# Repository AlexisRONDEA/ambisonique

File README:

Projet : Ambisonique
  
Collaborateurs : RONDEAU Alexis, SOULE Zeïck, BODET Amaury, VAN DE MOOSDIJK Martina, MILLASSEAU Adrien, LATHUILLERE Colin

	I / Introduction
	
Ce projet, initialement conçu par des troisièmes années, permet de connecter huit enceintes pour délivrer un son provenant de différentes directions.
Nos objectifs concernent l’encombrement et la qualité sonore de l’amplificateur audio. En effet, les enceintes sont pour l’instant alimentées par des alimentations de laboratoire, ce qui est peu pratique et prend de la place. De plus, le signal audio est transmis par un seul fil. Cette liaison asymétrique est la source de parasite sur le signal et donne lieu à une mauvaise qualité sonore. 
On se propose donc de remplacer la transmission du signal par une liaison symétrique différentielle, pour supprimer le plus de parasites possible. On change l’amplificateur actuel par un amplificateur de classe D pour améliorer la qualité sonore du signal en sortie. Enfin, on fait passer l’alimentation des enceintes par le câble transmettant le signal audio, pour alimenter les enceintes avec le réseau.
Pour cela on sépare ce projet en quatre modules et en deux PCB. Les deux premiers appartiendront au premier et le séparateur avec l’ampli audio seront sur le deuxième PCB.

Objectifs : 
- Créer un module modifiant le courant d'entrée du réseau 230V AC en 24V DC
- Créer un module qui additionne la partie continue de 24V au signal
- Créer un module qui sépare le signal et la puissance pour alimenter les enceintes
- Créer l’amplificateur de classe D
 
Le cahier des charges, le diagramme d’architecture, la présentation PDF du projet ainsi que les commandes des composants se trouvent dans le dossier « livrables ».
[clicl](livrables/Cahier des Charges - Ambisonique [2].pdf)
[clic me](https://github.com/AlexisRONDEA/ambisonique/blob/main/livrables/Cahier%20des%20Charges%20-%20Ambisonique%20%5B2%5D.pdf)
	II / Alimentation du circuit

Pour ce module on utilise les composants suivants :
-	Un connecteur MPT 0.5/2-2.54
-	Un transformateur PCB, 230V, 2 * 24V
-	Un pont redresseur monophasé
-	Un contrôleur DC/DC, synchrone, Buck, output 24V

Le transformateur permet de modifier la tension d’entrée du réseau de 230V alternatif en 24V alternatif. Le courant est ensuite envoyé dans le pont de diode redresseur qui renvoie une tension de 33V continu en sortie. Enfin, le contrôleur Buck abaisse la tension à 24V continu pour l’envoyer dans le module additionneur.

Dans un premier temps, pour créer ce module on voulait utiliser un montage avec un régulateur de tension. Cependant, ce circuit était assez vieux et donc pas assez performant par rapport à d’autres montages envisageables. Les pertes étaient trop importantes et c’est pour cela que nous avons décidé d’opter pour ce circuit actuel. 
De plus, notre circuit actuel devait utiliser les deux branches de sortie du transformateur qui fournit du 2x24V, car une fois 24V n’aurait pas était suffisant. Cependant la tension de sortie correspond à un courant alternatif, qui est donc redresser par le pont de diode ensuite à 33V continu. C’est pourquoi on n’utilise qu’une seule branche de sortie du transformateur.  

 Ce module fait partie du premier PCB, les fichiers utiles au PCB sont donc ambisoniqueAlim.sch et ambisoniqueAlim.brd. Les empreintes du contrôleur Buck et du transformateur ont été créé pour Eagle tandis que l’empreinte du pont redresseur a été téléchargée sur internet. 

	III / Additionneur

Pour ce module, on utilise les composants suivants : 

-	Deux transistors de puissance NPN TIP31A 
-	Deux connecteurs Jack 

On réalise un montage à collecteur commun en utilisant le TIP31A. Il permet d'obtenir en sortie, au niveau de l'émetteur et dans le même fil, le signal audio ainsi que les 24 V DC obtenus dans le module précédent. On assure la transmission par un seul câble XLR. On souhaite également avoir un courant de 1.5 A en sortie du transistor, d'où le choix d'un transistor de puissance pour réaliser ce montage. Enfin, on réalise ce montage deux fois, avec un signal audio positif puis négatif afin de pouvoir les soustraire et travailler en différentiel. L'objectif du différentiel est d'éviter les perturbations électromagnétiques, qui se répercutent sur les deux signaux. En les soustrayant, on efface alors les parasites. On souhaite également éviter d'impacter la valeur continue, en choisissant judicieusement la valeur des résistances. 

Nous avons pensé à réaliser ce module en utilisant un schéma additionneur avec un amplificateur opérationnel, néanmoins cela aurait été compliqué car il nous fallait avoir un courant conséquent en sortie, ce qui n'est pas possible avec un AOP. 

Ce module fait partie du premier PCB, les fichiers utiles au PCB sont donc "ambisoniqueAlim.sch" et "ambisoniqueAlim.brd".

 	IV / Séparateur 
 
Pour ce module on utilise les composants suivants :
-	Deux contrôleurs DC/DC, synchrone, Buck, output 12V

Pour ce module, on utilise des condensateurs. On utilise leur caractéristique de filtre pour séparer la composante continue et le signal. On souhaite séparer la composante continue afin de l'utiliser en tant qu'alimentation pour les enceintes, et d'utiliser la composante alternative pour l'amplifier dans le module suivant. Les deux câbles de puissance rentrent alors dans les contrôleurs Buck qui renvoient une tension de 12V. On fait se rejoindre les deux câbles, puis on les sépare pour alimenter le microprocesseur et les MOSFET. En effet, les MOSFET sont directement alimentés en 12V, tandis que la tension d’entrée du microprocesseur passe par un régulateur avant d’alimenter le microprocesseur en 3,3V. 

Pour ce module, on a dû recommander les contrôleurs Buck. En effet, ceux commandés ne pouvait que donner du 5V en sortie contrairement aux 12V voulus.

Ce module fait partie du second PCB, les fichiers utiles au PCB sont donc "ambisoniqueAmpli.sch" et "ambisoniqueAmpli.sch".

	V / Amplificateur audio

Pour ce module on utilise les composants suivants :
-	Un microcontrôleur STM32L412KBT6
-	Un MOSFET de puissance, Canal N, 20 V, 3.9 A, 0.025 Ohm
-	Un MOSFET de puissance, Canal P, 20 V, 3.2 A, 0.08 Ohm

L’objectif de cette partie du projet est de remplacer l’amplificateur audio déjà existant en le substituant par un microprocesseur. Ce dernier permet de créer une PWM qui rentre ensuite dans un amplificateur de classe D composé des deux MOSFET de puissance. Pour ce faire, on alimente le microprocesseur avec du 3,3V venant du module séparateur et les MOSFET en 12V. Le microprocesseur récupère le signal différentiel en entrée et le traite, pour retourner un signal simple avec le moins de parasites possible. Ensuite, le signal est comparé à un signal triangle, modélisé par un compteur TIMER sur le microprocesseur, pour générer la PWM. 

Nous voulions d’abord utiliser d’autres circuits, avec d’autres types d’amplificateur. Cependant, cet amplificateur de classe D est le plus performant. 
De plus, la programmation du microprocesseur n’est pas terminée.

Ce module fait partie du second PCB, les fichiers utiles au PCB sont donc "ambisoniqueAmpli.sch" et "ambisoniqueAmpli.sch". Les empreintes des MOSFET viennent d’internet, et celle du microprocesseur nous a été fournie en amont.

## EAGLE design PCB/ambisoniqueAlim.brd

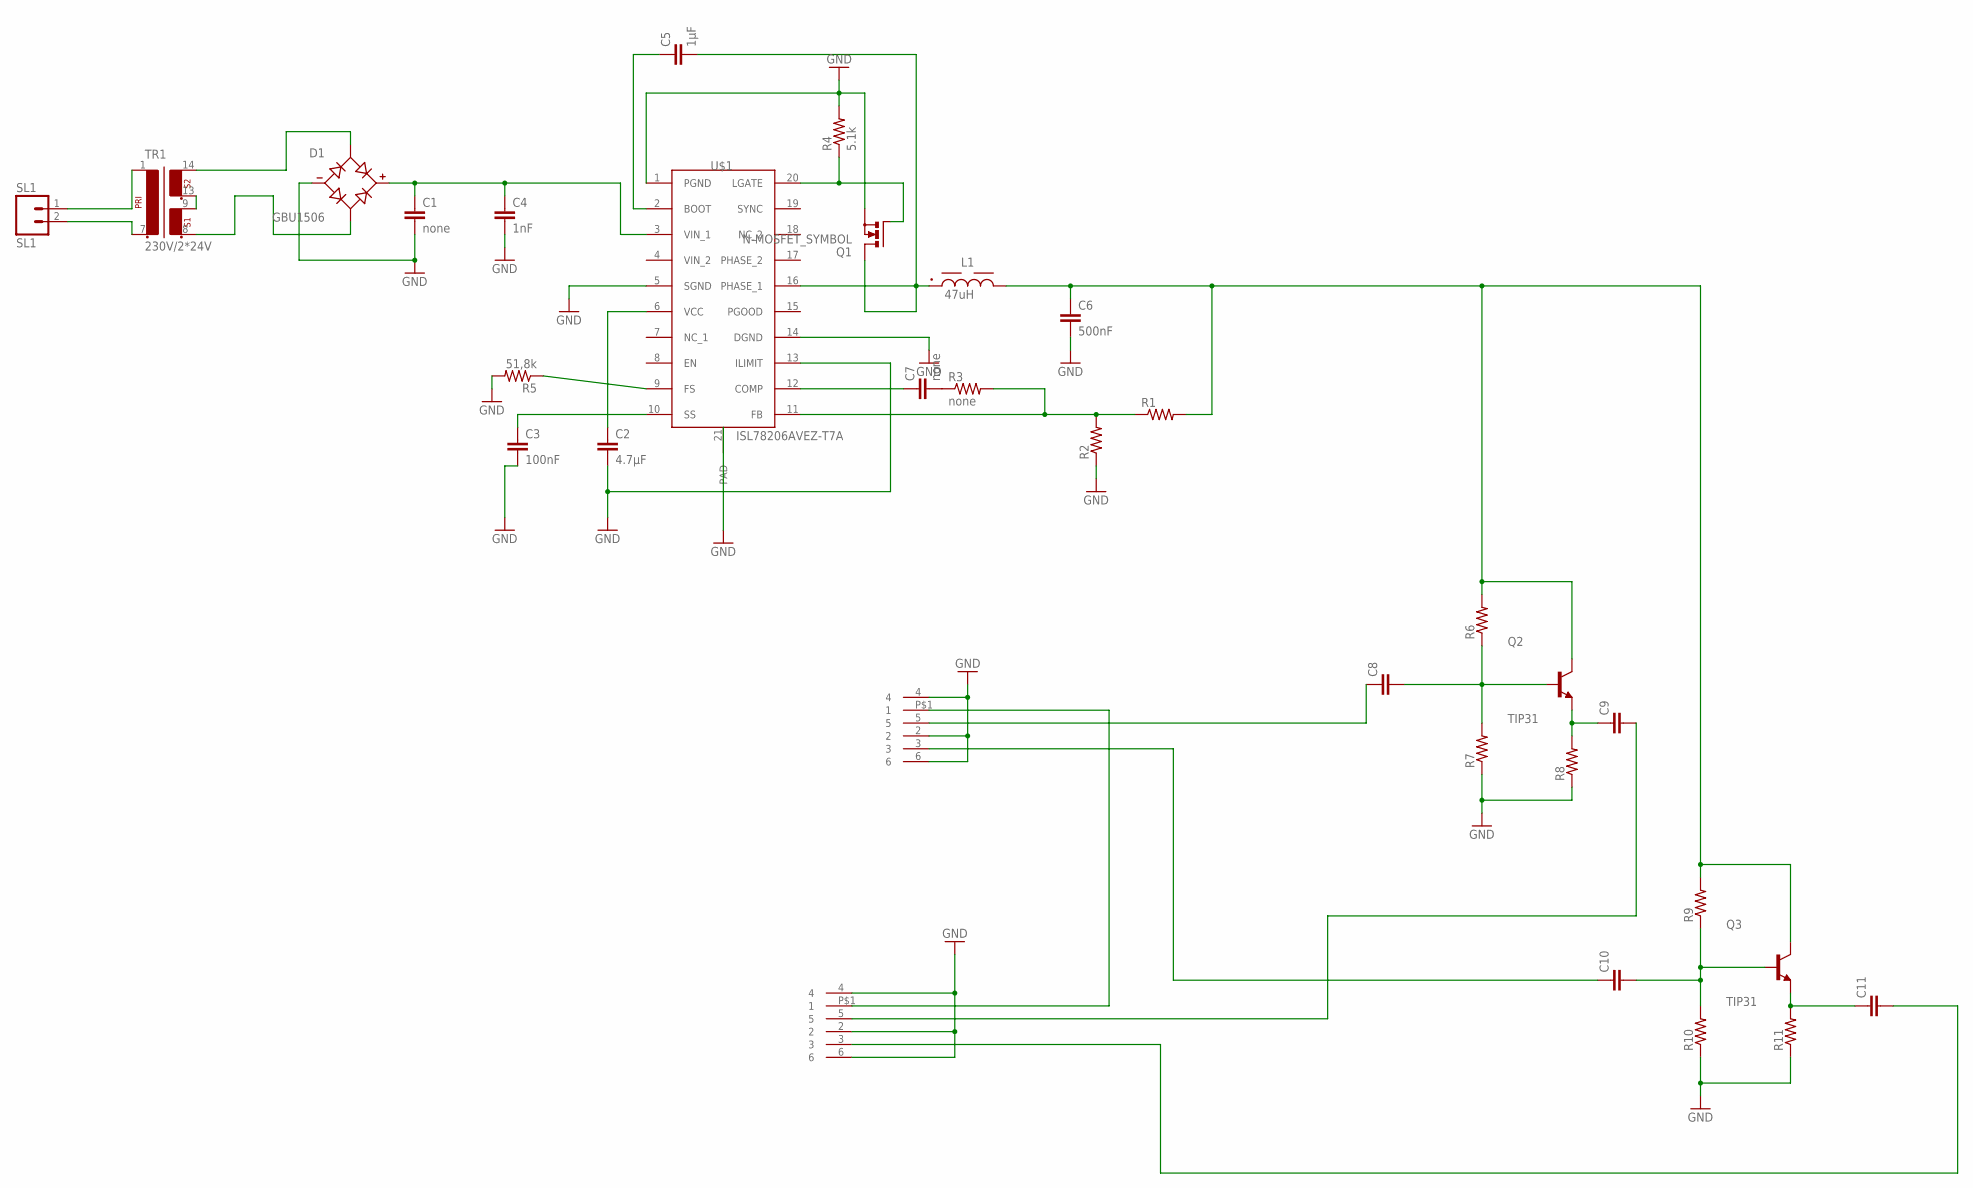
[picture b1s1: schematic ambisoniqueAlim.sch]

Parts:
C1, C7: none; C0603
C2: 4.7µF; C0603
C3: 100nF; C0603
C4: 1nF; C0603
C5: 1µF; C0603
C6: 500nF; C0603
C8, C9, C10, C11: C-EUC0603; C0603
D1: GBU1506; SIP343W114P508L2205H2134Q4
L1: 47uH; WE-PDA_1210
Q2, Q3: TIP31; TO254P1060X482X2222-3
R1, R2, R6, R7, R8, R9, R10, R11: R-US_R0603; R0603
R3: none; R0603
R4: 5.1k; R0603
R5: 51,8k; R0603
SL1: SL1; 02P
TR1: 230V/2*24V; EI60-2
U$1: ISL78206AVEZ-T7A; SOP65P640X110-21N
U$2, U$3: JACK6.35MMRSPRODEV; JACKRSPRO6.35MM

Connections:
GND: C1.2, C2.2, C3.2, C4.2, C6.2, D1.-, R2.1, R4.2, R5.2, R7.1, R8.1, R10.1, R11.1, U$1.1 (PGND), U$1.5 (SGND), U$1.13 (ILIMIT), U$1.14 (DGND), U$1.21 (PAD), U$2.2, U$2.4, U$2.6, U$3.2, U$3.4, U$3.6
unnamed: TR1.9 (4), TR1.13 (5)
unnamed: D1.AC1, TR1.14 (6)
unnamed: C2.1, U$1.6 (VCC)
unnamed: SL1.1, TR1.1
unnamed: SL1.2, TR1.7 (2)
unnamed: D1.AC2, TR1.8 (3)
unnamed: U$2.P$1 (1), U$3.P$1 (1)
unnamed: C1.1, C4.1, D1.+, U$1.3 (VIN_1)
unnamed: C3.1, U$1.10 (SS)
unnamed: C5.1, U$1.2 (BOOT)
unnamed: C10.2, Q3.1 (B), R9.1, R10.2
unnamed: C9.1, Q2.3 (E), R8.2
unnamed: R1.1, R2.2, R3.2, U$1.11 (FB)
unnamed: C7.1, U$1.12 (COMP)
unnamed: C7.2, R3.1
unnamed: R5.1, U$1.9 (FS)
unnamed: R4.1, U$1.20 (LGATE)
unnamed: C8.2, Q2.1 (B), R6.1, R7.2
unnamed: C9.2, U$3.5
unnamed: C11.1, Q3.3 (E), R11.2
unnamed: C6.1, L1.2, Q2.2 (C), Q3.2 (C), R1.2, R6.2, R9.2
unnamed: C5.2, L1.1, U$1.16 (PHASE_1)
unnamed: C11.2, U$3.3
unnamed: C10.1, U$2.3
unnamed: C8.1, U$2.5

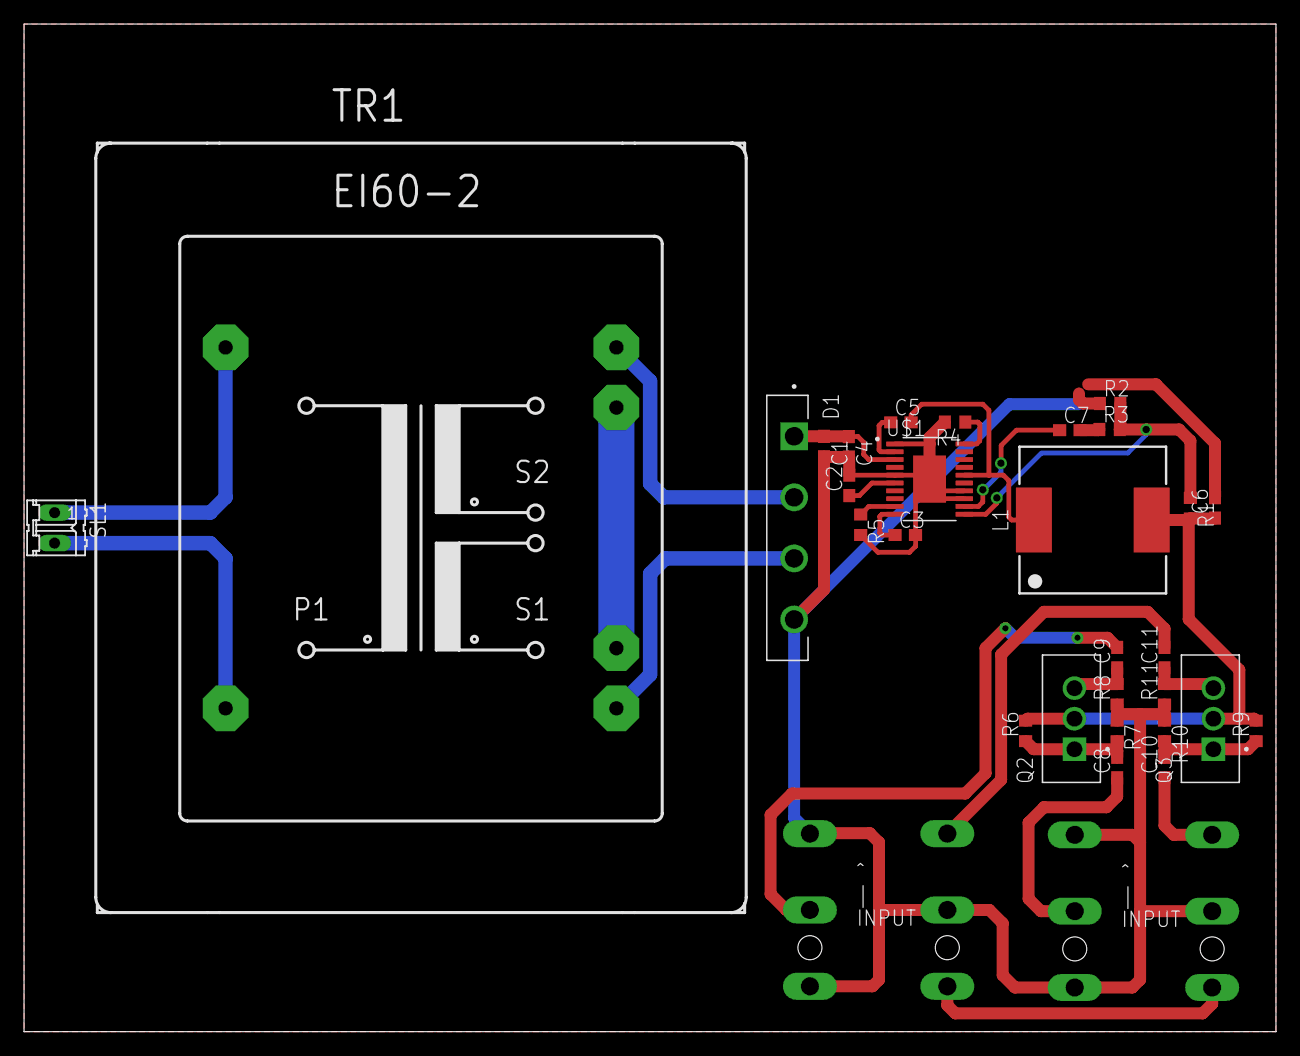
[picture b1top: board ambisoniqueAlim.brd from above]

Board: 2 copper layers, 104.1 x 83.8 mm, 31 parts (0 on the bottom side), 26 nets.

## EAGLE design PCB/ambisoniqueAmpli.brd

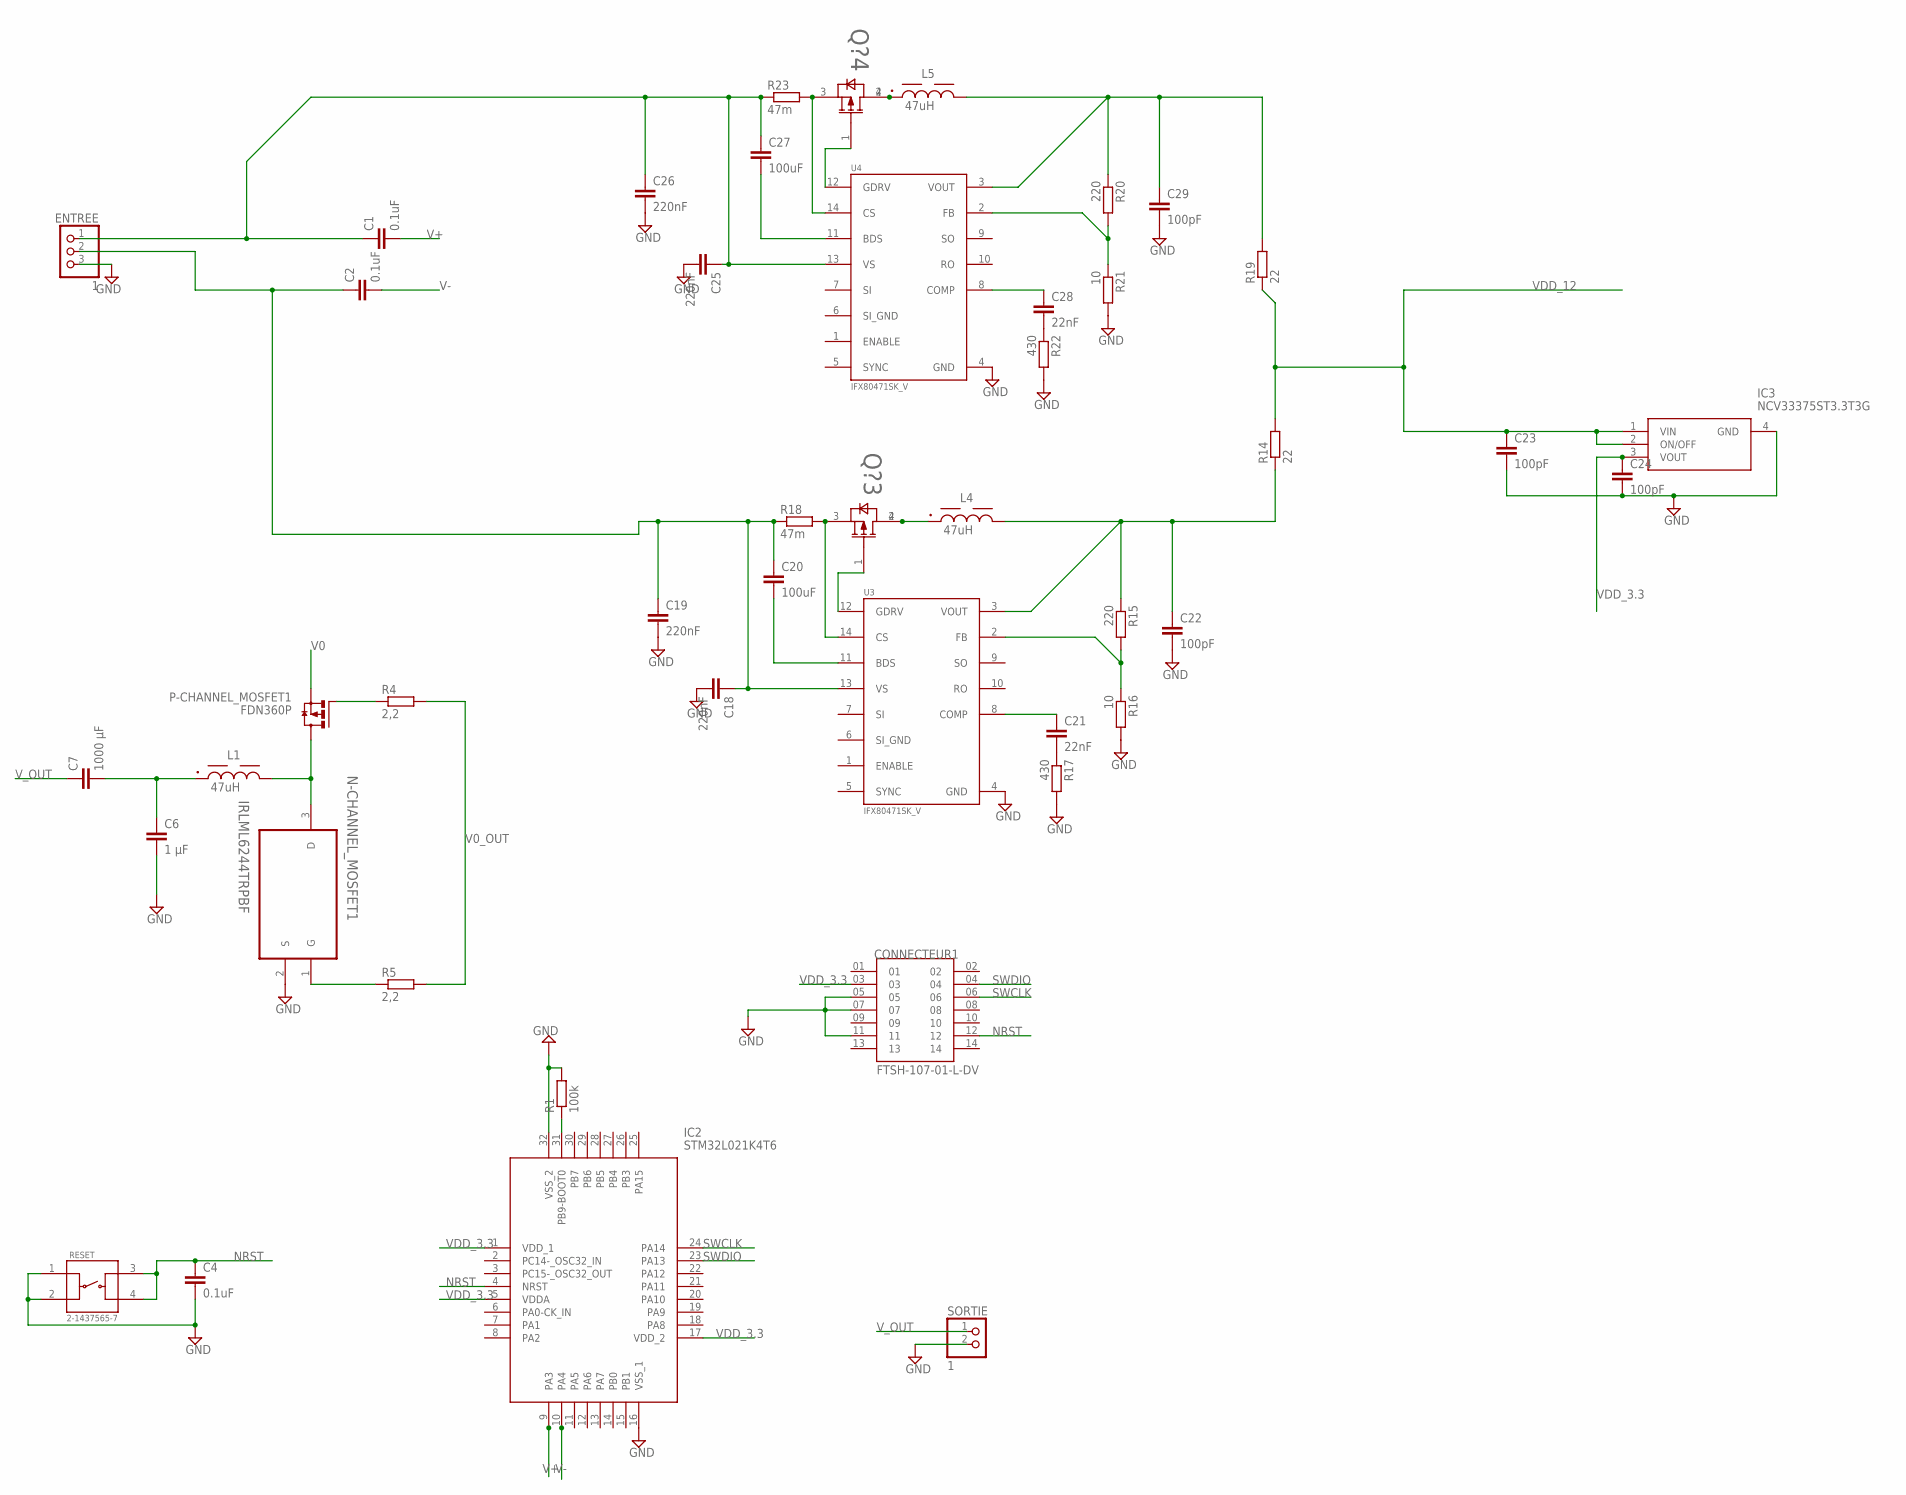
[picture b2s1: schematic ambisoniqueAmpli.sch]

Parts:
C1, C2, C4: 0.1uF; C0603
C6: 1 µF; C0603
C7: 1000 µF; C0603
C18, C19, C25, C26: 220nF; C0603
C20, C27: 100uF; C0603
C21, C28: 22nF; C0603
C22, C23, C24, C29: 100pF; C0603
CONNECTEUR1: FTSH-107-01-L-DV; SAMTEC_FTSH-107-01-L-DV
ENTREE: 1; 1X03
IC2: STM32L021K4T6; QFP80P900X900X160-32N
IC3: NCV33375ST3.3T3G; SOT230P700X175-4N
L1, L4, L5: 47uH; WE-PDA_1210
N-CHANNEL_MOSFET1: IRLML6244TRPBF; SOT95P237X112-3N
P-CHANNEL_MOSFET1: FDN360P; SUPER-SOT3
Q?3, Q?4: BSP613P; SOT230P700X170-4N
R1: 100k; R0603
R4, R5: 2,2; R0603
R14, R19: 22; R0603
R15, R20: 220; R0603
R16, R21: 10; R0603
R17, R22: 430; R0603
R18, R23: 47m; R0603
RESET: 2-1437565-7; SW_2-1437565-7
SORTIE: 1; 1X02
U3, U4: IFX80471SK_V; SOIC127P600X175-14N-8

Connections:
GND: C4.2, C6.2, C18.2, C19.2, C22.2, C23.2, C24.2, C25.2, C26.2, C29.2, CONNECTEUR1.05, CONNECTEUR1.07, CONNECTEUR1.11, ENTREE.3, IC2.16 (VSS_1), IC2.32 (VSS_2), IC3.4 (GND), N-CHANNEL_MOSFET1.2 (S), R1.2, R16.2, R17.2, R21.2, R22.2, RESET.1, RESET.2, SORTIE.2, U3.4 (GND), U4.4 (GND)
unnamed: C28.2, R22.1
unnamed: IC2.31 (PB9-BOOT0), R1.1
unnamed: C21.2, R17.1
unnamed: P-CHANNEL_MOSFET1.1 (G), R4.1
unnamed: L1.2, N-CHANNEL_MOSFET1.3 (D), P-CHANNEL_MOSFET1.3 (D)
unnamed: C6.1, C7.2, L1.1
unnamed: N-CHANNEL_MOSFET1.1 (G), R5.1
unnamed: Q?3.3 (SOURCE), R18.2, U3.14 (CS)
unnamed: Q?3.1 (GATE), U3.12 (GDRV)
unnamed: C20.2, U3.11 (BDS)
unnamed: L4.1, Q?3.2 (DRAIN_1), Q?3.4 (DRAIN_2)
unnamed: C21.1, U3.8 (COMP)
unnamed: R15.2, R16.1, U3.2 (FB)
unnamed: C22.1, L4.2, R14.1, R15.1, U3.3 (VOUT)
unnamed: Q?4.3 (SOURCE), R23.2, U4.14 (CS)
unnamed: Q?4.1 (GATE), U4.12 (GDRV)
unnamed: C27.2, U4.11 (BDS)
unnamed: L5.1, Q?4.2 (DRAIN_1), Q?4.4 (DRAIN_2)
unnamed: C28.1, U4.8 (COMP)
unnamed: R20.2, R21.1, U4.2 (FB)
unnamed: C29.1, L5.2, R19.2, R20.1, U4.3 (VOUT)
NRST: C4.1, CONNECTEUR1.12, IC2.4 (NRST), RESET.3, RESET.4
SI_GND: U3.6 (SI_GND), U4.6 (SI_GND)
SWCLK: CONNECTEUR1.06, IC2.24 (PA14)
SWDIO: CONNECTEUR1.04, IC2.23 (PA13)
V0: P-CHANNEL_MOSFET1.2 (S)
V0_OUT: R4.2, R5.2
V+: C1.2, IC2.9 (PA3)
V+_IN: C1.1, C25.1, C26.1, C27.1, ENTREE.1, R23.1, U4.13 (VS)
V-: C2.2, IC2.10 (PA4)
V-_IN: C2.1, C18.1, C19.1, C20.1, ENTREE.2, R18.1, U3.13 (VS)
VDD_3.3: C24.1, CONNECTEUR1.03, IC2.1 (VDD_1), IC2.5 (VDDA), IC2.17 (VDD_2), IC3.3 (VOUT)
VDD_12: C23.1, IC3.1 (VIN), IC3.2 (ON/OFF), R14.2, R19.1
V_OUT: C7.1, SORTIE.1

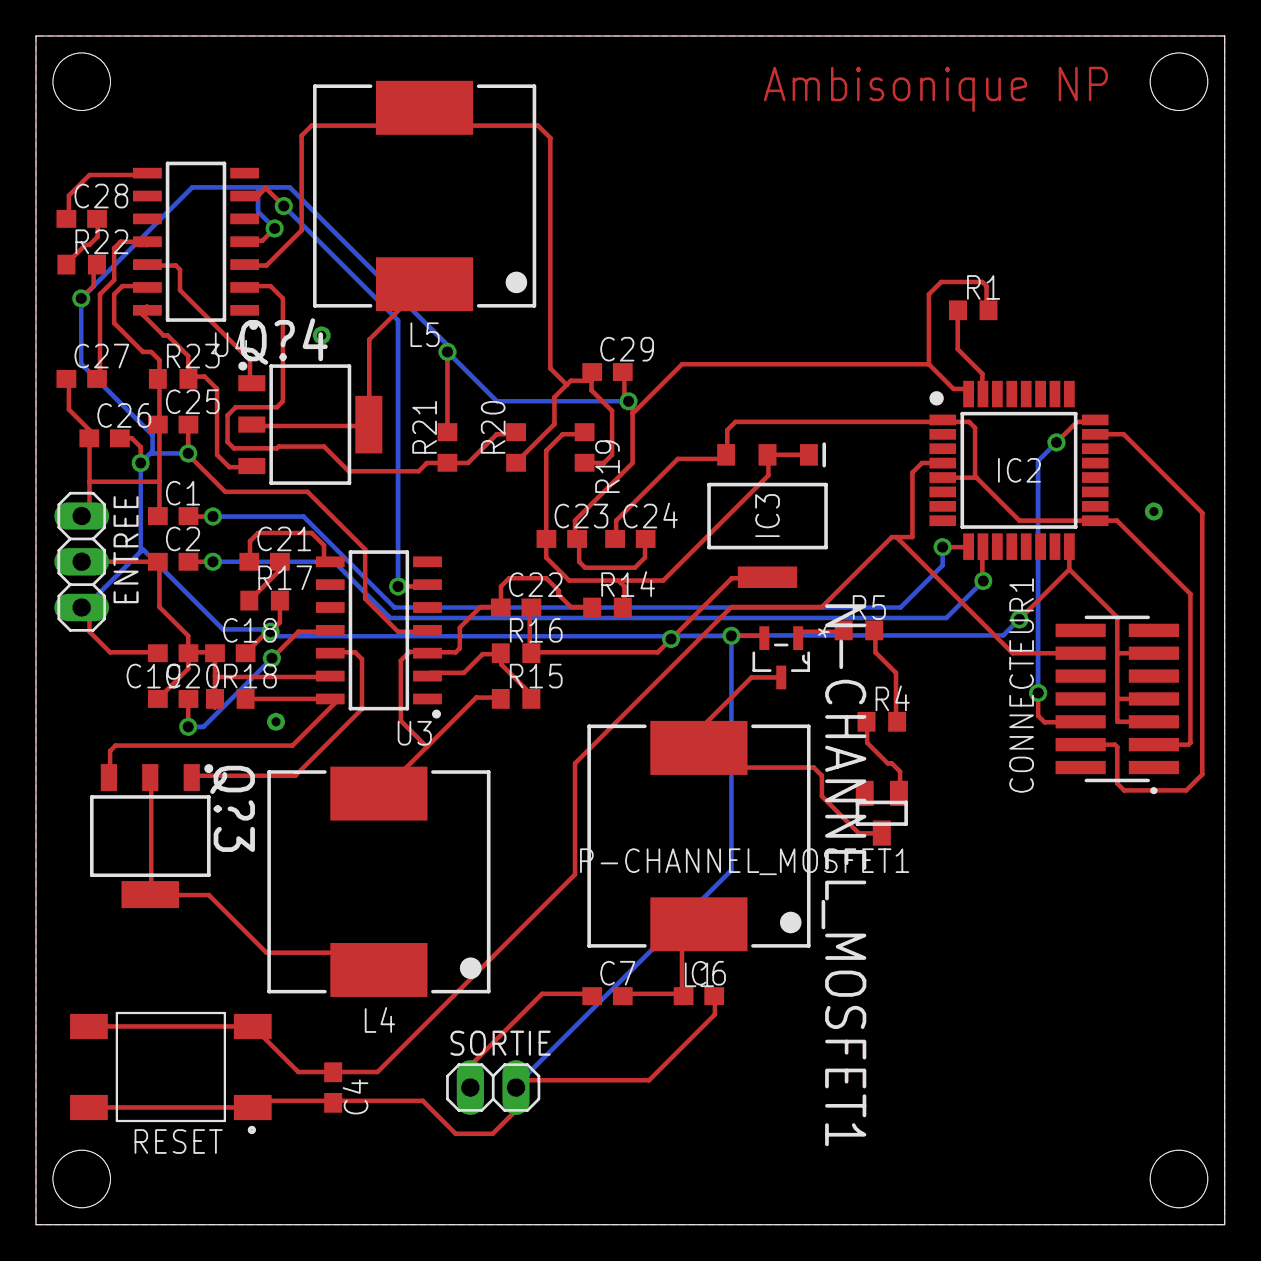
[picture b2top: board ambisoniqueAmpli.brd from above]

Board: 2 copper layers, 66.0 x 66.0 mm, 45 parts (0 on the bottom side), 34 nets.

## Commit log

2022-05-09 Add files via upload
    alim
2022-05-16 Create commandes des composants
2022-05-16 Create data
2022-05-16 Create pcd
2022-05-24 Create Truc
2022-06-05 Rename README to README.md

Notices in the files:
parts and their libraries:
Eagle_WE-PDA: Copyright: Würth Elektronik
